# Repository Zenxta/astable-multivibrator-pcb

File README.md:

# Astable Multivibrator Circuit

This is a PCB design for a transistor-based astable multivibrator, a simple square wave oscillator. The circuit is configured to use two NPN transistors in a common emitter configuration, which causes two LEDs to flash alternately, demonstrating a 180-degree phase shift. The entire design was created using KiCad software.

## Components

| Component | Value | Description |
| :--- | :--- | :--- |
| **Transistors** | 2N3904 (Q1, Q2) | Two NPN BJTs. |
| **Resistors** | 300 Ω (R1, R4) | Resistors for the LEDs. |
| | 47 kΩ (R2, R3) | Resistors to control transistor's base voltage and timing of the oscillation. |
| **Capacitors** | 10 µF (C1, C2) | Timing capacitors that charge and discharge alternatively to create the oscillation. |
| **Diodes** | LED (D1, D2) | LEDs that provide a visual indication of the output. |
| **Switch** | SPDT (SW1) | Single Pole Double Throw switch to control the circuit. |
| **Power** | Battery (BT1) | A power source for the circuit. |
| **Mounting** | H1, H2, H3, H4 | Four mounting holes for holding the PCB. |

## Design & Gerber Files

All design and gerber files for this project are included in the repository (files added at top) and can be opened with KiCad. 

* **Schematic:** `schematic.kicad_sch`
* **PCB Layout:** `pcb board.kicad_pcb`
* **Gerber Files:** `gerber.zip`

## Images

### Schematic Diagram

### PCB Layout

### 3-D View of PCB (front and back)

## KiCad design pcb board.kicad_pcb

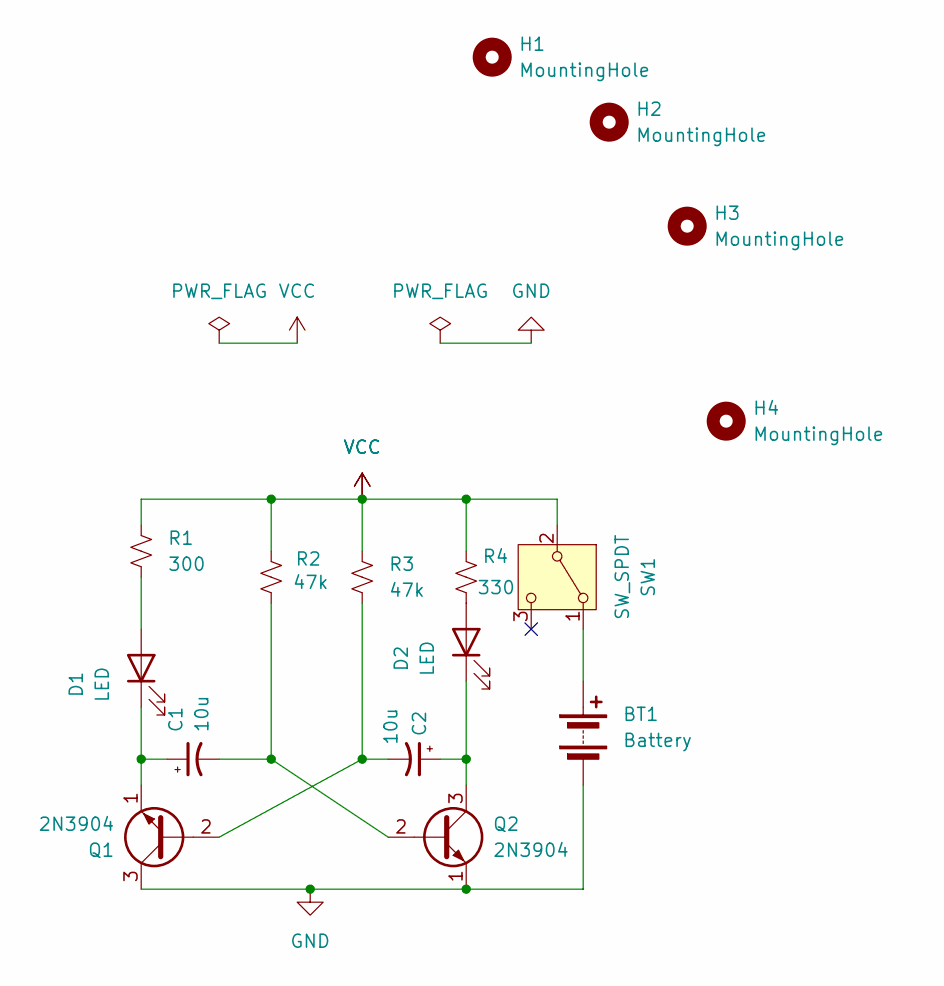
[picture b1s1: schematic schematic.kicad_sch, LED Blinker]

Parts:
BT1: Battery; BatteryHolder_Keystone_2479_3xAAA
C1, C2: 10u; CP_Radial_D6.3mm_P2.50mm
D1, D2: LED; LED_D5.0mm
H1, H2, H3, H4: MountingHole; MountingHole_3.2mm_M3
Q1, Q2: 2N3904; TO-92_Inline
R1: 300; R_Axial_DIN0207_L6.3mm_D2.5mm_P10.16mm_Horizontal
R2, R3: 47k; R_Axial_DIN0207_L6.3mm_D2.5mm_P10.16mm_Horizontal
R4: 330; R_Axial_DIN0207_L6.3mm_D2.5mm_P10.16mm_Horizontal
SW1: SW_SPDT; SW_E-Switch_EG1224_SPDT_Angled

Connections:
GND: BT1.2 (-), Q1.3 (C), Q2.1 (E)
unnamed: BT1.1 (+), SW1.1 (A)
unnamed: D1.2 (A), R1.2
unnamed: C1.1, D1.1 (K), Q1.1 (E)
unnamed: D2.2 (A), R4.2
unnamed: C2.1, D2.1 (K), Q2.3 (C)
unnamed: C2.2, Q1.2 (B), R3.2
unnamed: C1.2, Q2.2 (B), R2.2
VCC: R1.1, R2.1, R3.1, R4.1, SW1.2 (B)

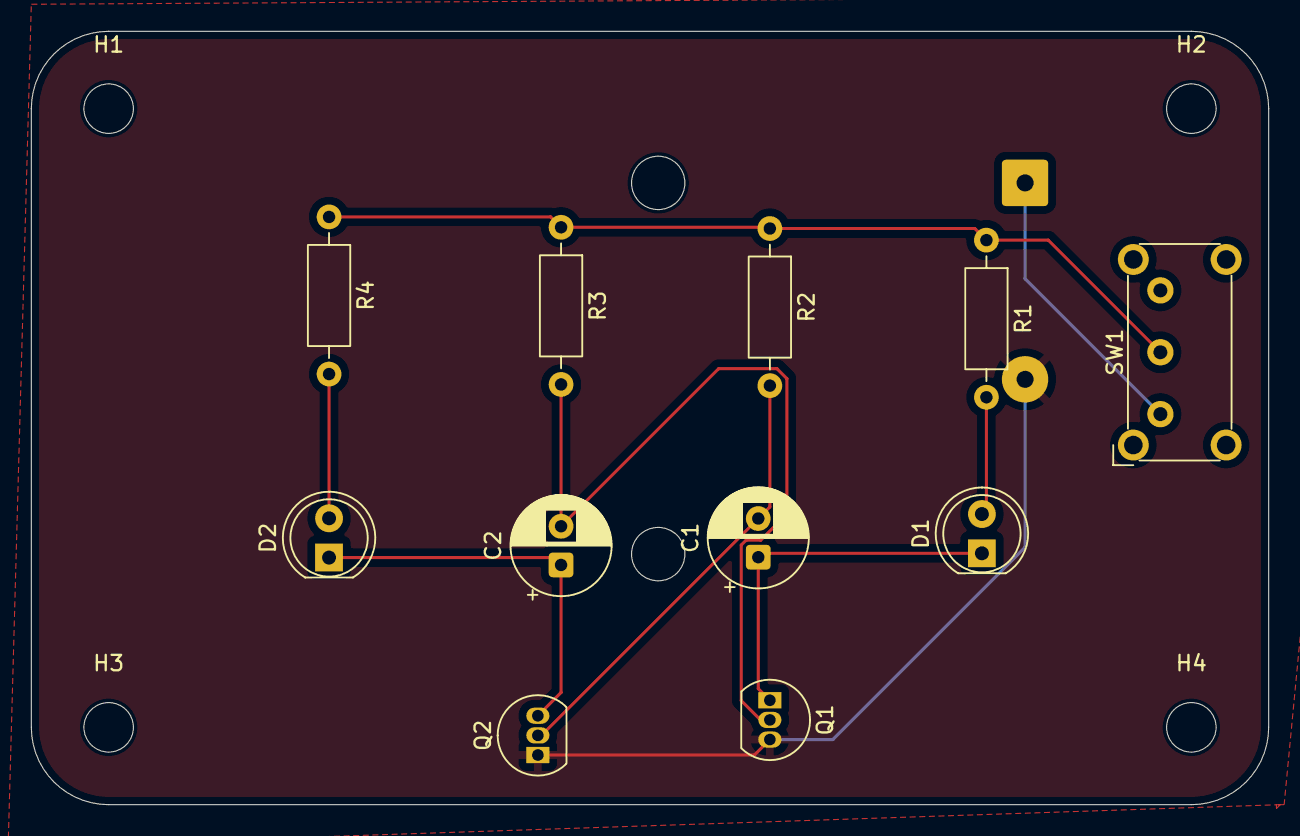
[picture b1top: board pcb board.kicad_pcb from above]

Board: 2 copper layers, 80.0 x 50.0 mm, 16 parts (1 on the bottom side), 9 nets.

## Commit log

2025-07-18 README.md
2025-11-20 Fix links to design files in README
2025-11-20 Clarify design files are downloadable with links
    Updated README to clarify that design files are downloadable and provided direct download links.
2025-11-20 Clarify design files availability in README
    Updated the README to clarify the availability of design files and modified the format for listing downloadable files.
2025-11-21 README.md
    Updated section title and improved clarity of design file description.
2025-11-28 Revise README for Alarm Security System project
